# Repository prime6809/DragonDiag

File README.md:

# DragonDiag
Diagnotic card for the Dragon 32/64 and Tandy CoCo 1,2,3.

Included is the Hardware design files created in Eagle, these should be 
compatible with any version of Eagale 6.x or later. Recent versions of 
KiCad should also be able to successfully import them.
Folder: hardware

The Verilog source for the onboard XC95144XL CPLD. This can be built with
Xilinx WebPack 14.7.
Folder: cpld

The 6809 source to the diagnostic ROM generally programed into the first 
8K of the onboard flash rom. To assemble this you will need lwasm available
from http://www.lwtools.ca/ You will also need a nnix compatible make utility
I generally use cygwin, but it should be builable under Linux / Macos or 
any unix like environment with the correct tools.
Folder: src

The stl files for a case for both the diag board and the LCD display are
also provided along the the FreeCAD source files.
Folder: case

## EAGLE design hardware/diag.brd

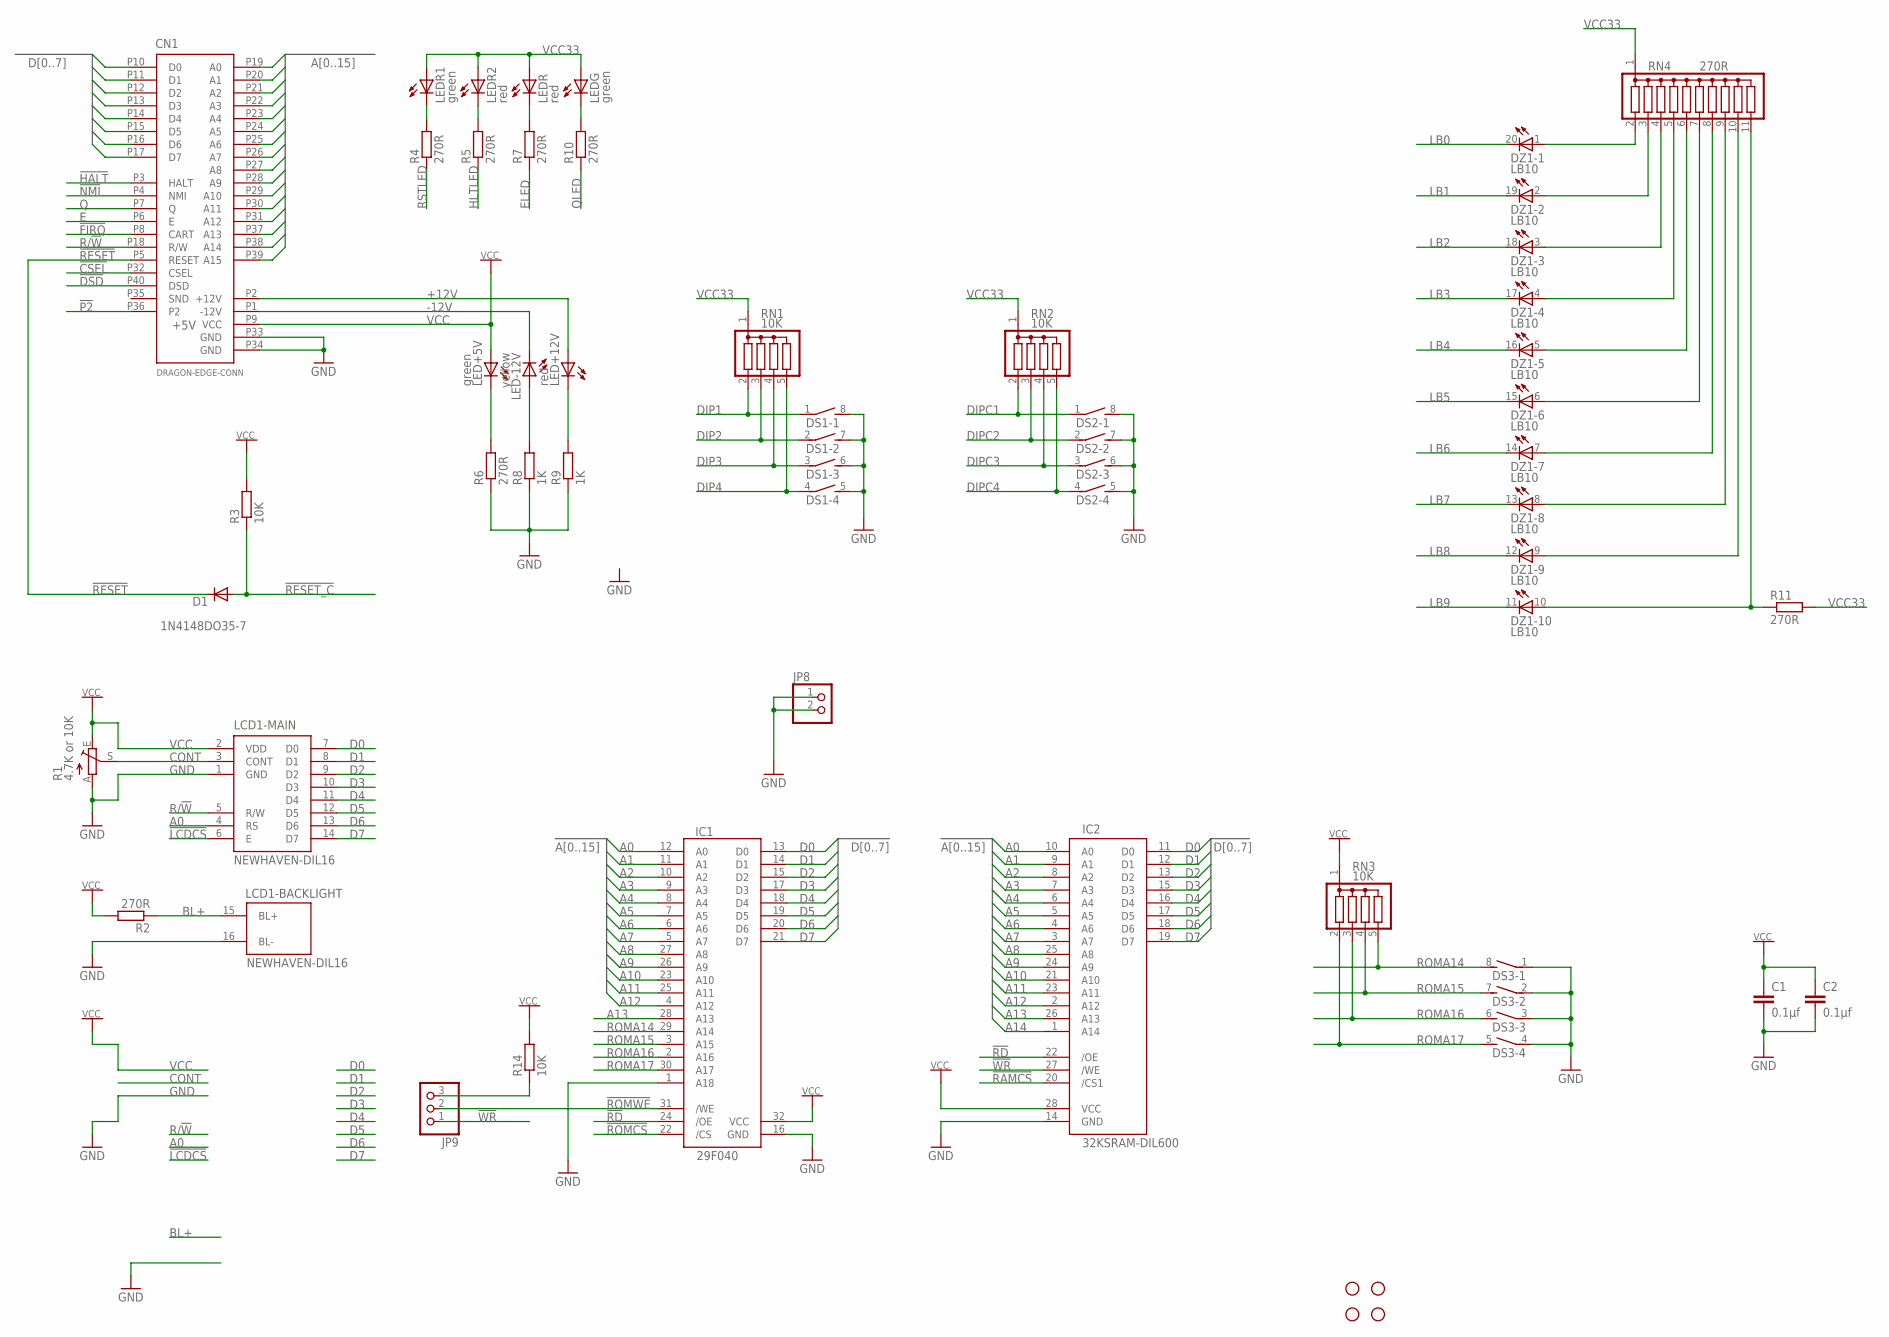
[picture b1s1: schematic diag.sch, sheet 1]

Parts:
C1, C2: 0.1µf; C025-025X050
CN1: DRAGON-EDGE-CONN; EDGE-40-01
D1: 1N4148DO35-7; DO35-7
DS1, DS2, DS3: DIP04S
DZ1: LB10
IC1: 29F040; DIL32
IC2: 32KSRAM-DIL600; DIL28-6
JP1, JP2, JP3, JP4: STAND-OFF
JP8: PINHD-1X2; 1X02
JP9: PINHD-1X3; 1X03
LCD1: NEWHAVEN-DIL16; 2X08
LED+5V: green; LED3MM
LED+12V: red; LED3MM
LED-12V: yellow; LED3MM
LEDG: green; LED3MM
LEDR, LEDR2: red; LED3MM
LEDR1: green; LED3MM
R1: 4.7K or 10K; CA9V
R2, R4, R5, R6, R7, R10, R11: 270R; 0207/10
R3: 10K; 0204/7
R8, R9: 1K; 0207/10
R14: 10K; 0207/10
RN1, RN2, RN3: 10K; SIL5
RN4: 270R; SIL11

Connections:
!CSEL: CN1.P32 (CSEL); also elsewhere on the board
!DSD: CN1.P40 (DSD); also elsewhere on the board
!FIRQ: CN1.P8 (CART); also elsewhere on the board
!HALT: CN1.P3 (HALT); also elsewhere on the board
!LCDCS: LCD1.6 (E); also elsewhere on the board
!NMI: CN1.P4 (NMI); also elsewhere on the board
!P2: CN1.P36 (P2); also elsewhere on the board
!RAMCS: IC2.20 (/CS1); also elsewhere on the board
!RD: IC1.24 (/OE), IC2.22 (/OE); also elsewhere on the board
!RESET: CN1.P5 (RESET), D1.C
!RESET_C: D1.A, R3.1; also elsewhere on the board
!ROMCS: IC1.22 (/CS); also elsewhere on the board
!ROMWE: IC1.31 (/WE), JP9.2
!WR: IC2.27 (/WE), JP9.1; also elsewhere on the board
+12V: CN1.P2 (+12V), LED+12V.A
-12V: CN1.P1 (-12V), LED-12V.K (C)
A0: CN1.P19 (A0), IC1.12 (A0), IC2.10 (A0), LCD1.4 (RS); also elsewhere on the board
A1: CN1.P20 (A1), IC1.11 (A1), IC2.9 (A1); also elsewhere on the board
A2: CN1.P21 (A2), IC1.10 (A2), IC2.8 (A2); also elsewhere on the board
A3: CN1.P22 (A3), IC1.9 (A3), IC2.7 (A3); also elsewhere on the board
A4: CN1.P23 (A4), IC1.8 (A4), IC2.6 (A4); also elsewhere on the board
A5: CN1.P24 (A5), IC1.7 (A5), IC2.5 (A5); also elsewhere on the board
A6: CN1.P25 (A6), IC1.6 (A6), IC2.4 (A6); also elsewhere on the board
A7: CN1.P26 (A7), IC1.5 (A7), IC2.3 (A7); also elsewhere on the board
A8: CN1.P27 (A8), IC1.27 (A8), IC2.25 (A8); also elsewhere on the board
A9: CN1.P28 (A9), IC1.26 (A9), IC2.24 (A9); also elsewhere on the board
A10: CN1.P29 (A10), IC1.23 (A10), IC2.21 (A10); also elsewhere on the board
A11: CN1.P30 (A11), IC1.25 (A11), IC2.23 (A11); also elsewhere on the board
A12: CN1.P31 (A12), IC1.4 (A12), IC2.2 (A12); also elsewhere on the board
A13: CN1.P37 (A13), IC1.28 (A13), IC2.26 (A13); also elsewhere on the board
A14: CN1.P38 (A14), IC2.1 (A14); also elsewhere on the board
A15: CN1.P39 (A15); also elsewhere on the board
BL+: LCD1.15 (BL+), R2.1
CONT: LCD1.3 (CONT), R1.S
D0: CN1.P10 (D0), IC1.13 (D0), IC2.11 (D0), LCD1.7 (D0); also elsewhere on the board
D1: CN1.P11 (D1), IC1.14 (D1), IC2.12 (D1), LCD1.8 (D1); also elsewhere on the board
D2: CN1.P12 (D2), IC1.15 (D2), IC2.13 (D2), LCD1.9 (D2); also elsewhere on the board
D3: CN1.P13 (D3), IC1.17 (D3), IC2.15 (D3), LCD1.10 (D3); also elsewhere on the board
D4: CN1.P14 (D4), IC1.18 (D4), IC2.16 (D4), LCD1.11 (D4); also elsewhere on the board
D5: CN1.P15 (D5), IC1.19 (D5), IC2.17 (D5), LCD1.12 (D5); also elsewhere on the board
D6: CN1.P16 (D6), IC1.20 (D6), IC2.18 (D6), LCD1.13 (D6); also elsewhere on the board
D7: CN1.P17 (D7), IC1.21 (D7), IC2.19 (D7), LCD1.14 (D7); also elsewhere on the board
DIP1: DS1.1, RN1.2; also elsewhere on the board
DIP2: DS1.2 (1), RN1.3; also elsewhere on the board
DIP3: DS1.3 (1), RN1.4; also elsewhere on the board
DIP4: DS1.4 (1), RN1.5; also elsewhere on the board
DIPC1: DS2.1, RN2.2; also elsewhere on the board
DIPC2: DS2.2 (1), RN2.3; also elsewhere on the board
DIPC3: DS2.3 (1), RN2.4; also elsewhere on the board
DIPC4: DS2.4 (1), RN2.5; also elsewhere on the board
E: CN1.P6 (E); also elsewhere on the board
ELED: R7.1; also elsewhere on the board
GND: C1.2, C2.2, CN1.P33 (GND), CN1.P34 (GND), DS1.5 (2), DS1.6 (2), DS1.7 (2), DS1.8 (2), DS2.5 (2), DS2.6 (2), DS2.7 (2), DS2.8 (2), DS3.1, DS3.2 (1), DS3.3 (1), DS3.4 (1), IC1.1 (A18), IC1.16 (GND), IC2.14 (GND), JP8.1, JP8.2, LCD1.1 (GND), LCD1.16 (BL-), R1.A, R6.1, R8.1, R9.1; also elsewhere on the board
HLTLED: R5.1; also elsewhere on the board
LB0: DZ1.20 (C); also elsewhere on the board
LB1: DZ1.19 (C); also elsewhere on the board
LB2: DZ1.18 (C); also elsewhere on the board
LB3: DZ1.17 (C); also elsewhere on the board
LB4: DZ1.16 (C); also elsewhere on the board
LB5: DZ1.15 (C); also elsewhere on the board
LB6: DZ1.14 (C); also elsewhere on the board
LB7: DZ1.13 (C); also elsewhere on the board
LB8: DZ1.12 (C); also elsewhere on the board
LB9: DZ1.11 (C); also elsewhere on the board
unnamed: LED+12V.K (C), R9.2
unnamed: LED+5V.K (C), R6.2
unnamed: DZ1.1 (A), RN4.2
unnamed: DZ1.2 (A), RN4.3
unnamed: LED-12V.A, R8.2
unnamed: DZ1.3 (A), RN4.4
unnamed: DZ1.4 (A), RN4.5
unnamed: DZ1.5 (A), RN4.6
unnamed: DZ1.6 (A), RN4.7
unnamed: LEDR.K (C), R7.2
unnamed: DZ1.7 (A), RN4.8
unnamed: DZ1.8 (A), RN4.9
unnamed: LEDG.K (C), R10.2
unnamed: DZ1.9 (A), RN4.10
unnamed: DZ1.10 (A), R11.1, RN4.11
unnamed: LEDR1.K (C), R4.2
unnamed: LEDR2.K (C), R5.2
unnamed: JP9.3, R14.1
Q: CN1.P7 (Q); also elsewhere on the board
QLED: R10.1; also elsewhere on the board
R/!W: CN1.P18 (R/W), LCD1.5 (R/W); also elsewhere on the board
ROMA14: DS3.8 (2), IC1.29 (A14), RN3.5
ROMA15: DS3.7 (2), IC1.3 (A15), RN3.4
ROMA16: DS3.6 (2), IC1.2 (A16), RN3.3
ROMA17: DS3.5 (2), IC1.30 (A17), RN3.2
RSTLED: R4.1; also elsewhere on the board
VCC: C1.1, C2.1, CN1.P9 (VCC), IC1.32 (VCC), IC2.28 (VCC), LCD1.2 (VDD), LED+5V.A, R1.E, R2.2, R3.2, R14.2, RN3.1; also elsewhere on the board
VCC33: LEDG.A, LEDR.A, LEDR1.A, LEDR2.A, R11.2, RN1.1, RN2.1, RN4.1; also elsewhere on the board

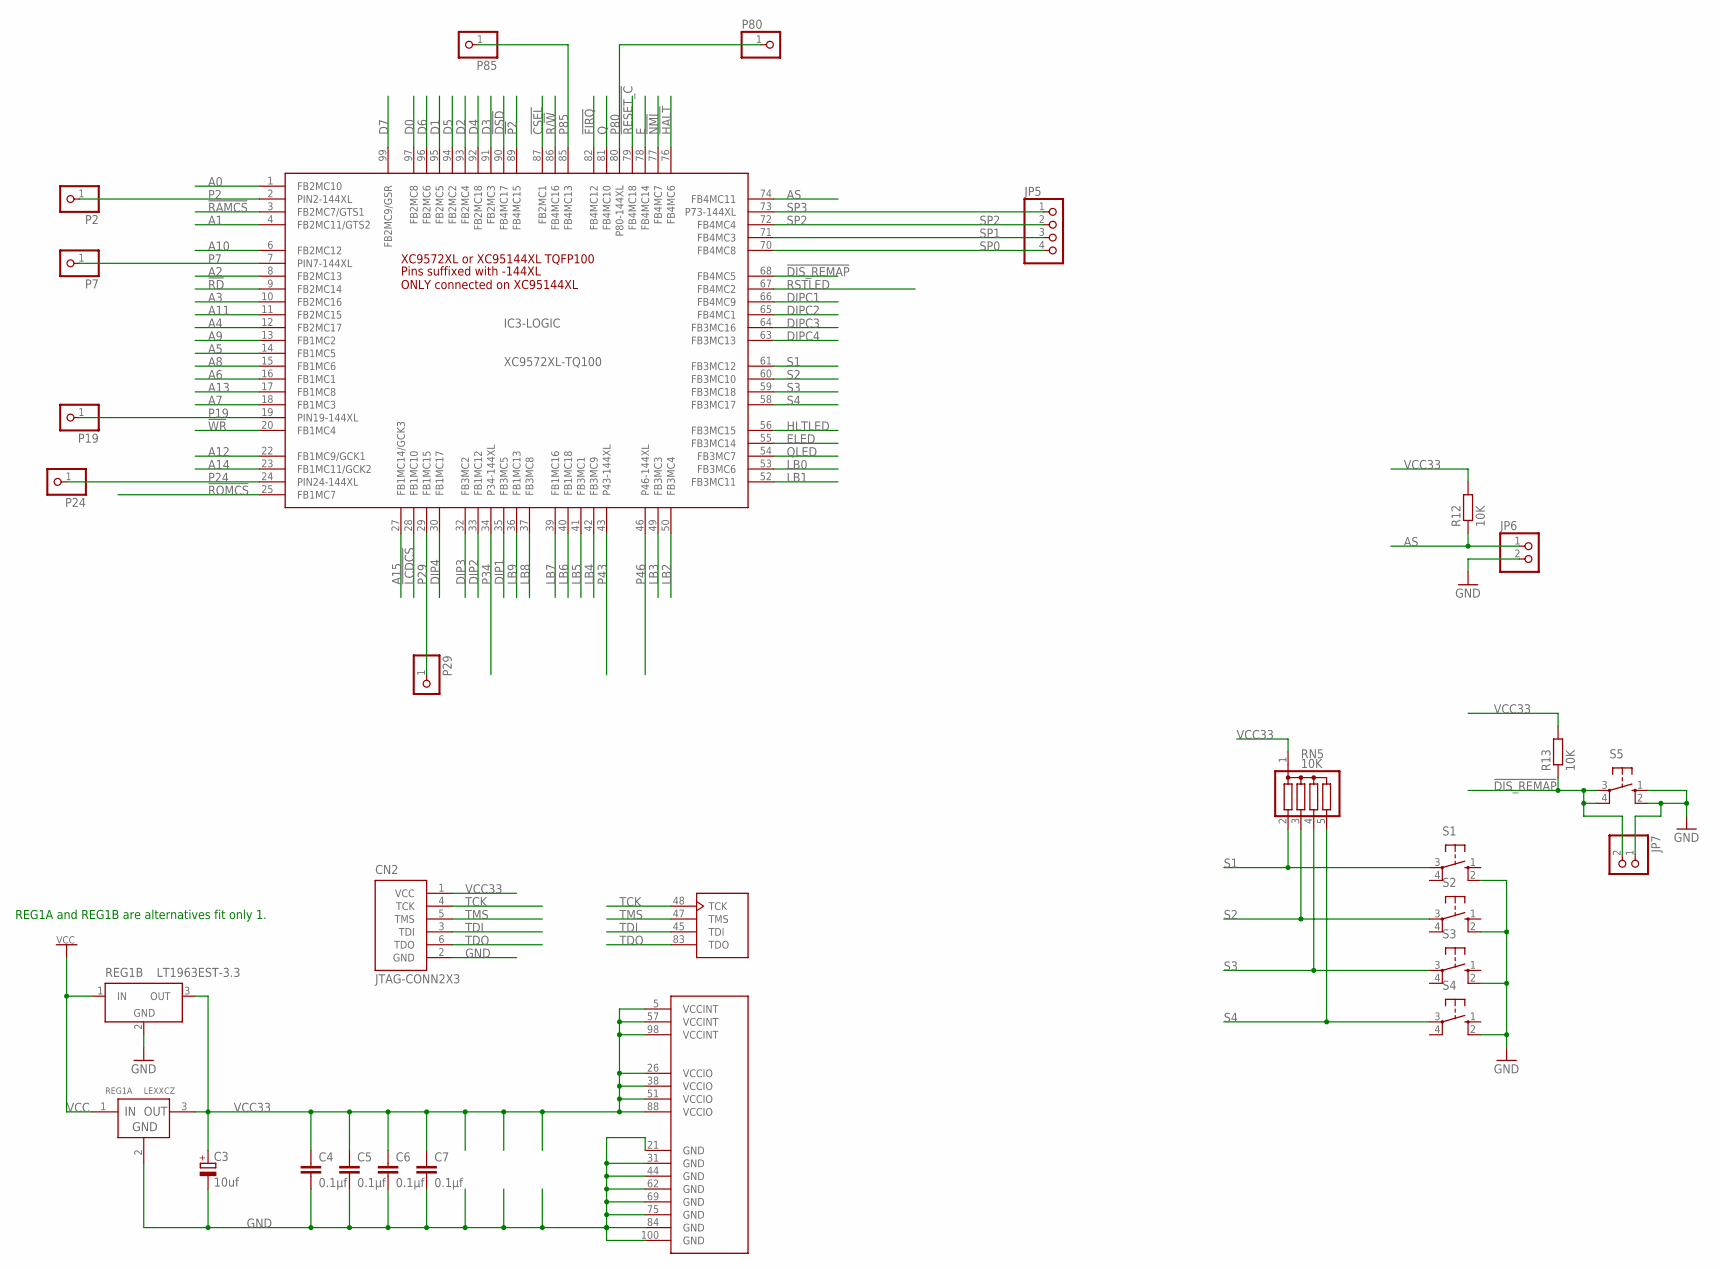
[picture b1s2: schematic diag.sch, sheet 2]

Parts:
C3: 10uf; TT2D7
C4, C5, C6, C7: 0.1µf; C025-025X050
CN2: JTAG-CONN2X3; 2X3
IC3: XC9572XL-TQ100; TQ100
JP5: PINHD-1X4; 1X04
JP6, JP7: PINHD-1X2; 1X02
P2, P7, P19, P24, P29, P80, P85: PINHD-1X1; 1X01
R12, R13: 10K; 0207/10
REG1A: LEXXCZ; TO92-
REG1B: LT1963EST-3.3; SOT223
RN5: 10K; SIL5
S1, S2, S3, S4, S5: 10-XX; B3F-10XX

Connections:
!CSEL: IC3.87 (FB2MC1); also elsewhere on the board
!DIS_REMAP: IC3.68 (FB4MC5), JP7.2, R13.1, S5.3, S5.4 (P1)
!DSD: IC3.90 (FB4MC17); also elsewhere on the board
!FIRQ: IC3.82 (FB4MC12); also elsewhere on the board
!HALT: IC3.76 (FB4MC6); also elsewhere on the board
!LCDCS: IC3.28 (FB1MC10); also elsewhere on the board
!NMI: IC3.77 (FB4MC7); also elsewhere on the board
!P2: IC3.89 (FB4MC15); also elsewhere on the board
!RAMCS: IC3.3 (FB2MC7/GTS1); also elsewhere on the board
!RD: IC3.9 (FB2MC14); also elsewhere on the board
!RESET_C: IC3.79 (FB4MC18); also elsewhere on the board
!ROMCS: IC3.25 (FB1MC7); also elsewhere on the board
!WR: IC3.20 (FB1MC4); also elsewhere on the board
A0: IC3.1 (FB2MC10); also elsewhere on the board
A1: IC3.4 (FB2MC11/GTS2); also elsewhere on the board
A2: IC3.8 (FB2MC13); also elsewhere on the board
A3: IC3.10 (FB2MC16); also elsewhere on the board
A4: IC3.12 (FB2MC17); also elsewhere on the board
A5: IC3.14 (FB1MC5); also elsewhere on the board
A6: IC3.16 (FB1MC1); also elsewhere on the board
A7: IC3.18 (FB1MC3); also elsewhere on the board
A8: IC3.15 (FB1MC6); also elsewhere on the board
A9: IC3.13 (FB1MC2); also elsewhere on the board
A10: IC3.6 (FB2MC12); also elsewhere on the board
A11: IC3.11 (FB2MC15); also elsewhere on the board
A12: IC3.22 (FB1MC9/GCK1); also elsewhere on the board
A13: IC3.17 (FB1MC8); also elsewhere on the board
A14: IC3.23 (FB1MC11/GCK2); also elsewhere on the board
A15: IC3.27 (FB1MC14/GCK3); also elsewhere on the board
AS: IC3.74 (FB4MC11), JP6.1, R12.1
D0: IC3.97 (FB2MC8); also elsewhere on the board
D1: IC3.95 (FB2MC5); also elsewhere on the board
D2: IC3.93 (FB2MC4); also elsewhere on the board
D3: IC3.91 (FB2MC3); also elsewhere on the board
D4: IC3.92 (FB2MC18); also elsewhere on the board
D5: IC3.94 (FB2MC2); also elsewhere on the board
D6: IC3.96 (FB2MC6); also elsewhere on the board
D7: IC3.99 (FB2MC9/GSR); also elsewhere on the board
DIP1: IC3.35 (FB3MC5); also elsewhere on the board
DIP2: IC3.33 (FB1MC12); also elsewhere on the board
DIP3: IC3.32 (FB3MC2); also elsewhere on the board
DIP4: IC3.30 (FB1MC17); also elsewhere on the board
DIPC1: IC3.66 (FB4MC9); also elsewhere on the board
DIPC2: IC3.65 (FB4MC1); also elsewhere on the board
DIPC3: IC3.64 (FB3MC16); also elsewhere on the board
DIPC4: IC3.63 (FB3MC13); also elsewhere on the board
E: IC3.78 (FB4MC14); also elsewhere on the board
ELED: IC3.55 (FB3MC14); also elsewhere on the board
GND: C3.-, C4.2, C5.2, C6.2, C7.2, CN2.2 (GND), IC3.21 (GND), IC3.31 (GND), IC3.44 (GND), IC3.62 (GND), IC3.69 (GND), IC3.75 (GND), IC3.84 (GND), IC3.100 (GND), JP6.2, JP7.1, REG1A.2 (GND), REG1B.2 (GND), REG1B.4 (GND), S1.2 (S1), S2.2 (S1), S3.2 (S1), S4.2 (S1), S5.1 (S), S5.2 (S1); also elsewhere on the board
HLTLED: IC3.56 (FB3MC15); also elsewhere on the board
LB0: IC3.53 (FB3MC6); also elsewhere on the board
LB1: IC3.52 (FB3MC11); also elsewhere on the board
LB2: IC3.50 (FB3MC4); also elsewhere on the board
LB3: IC3.49 (FB3MC3); also elsewhere on the board
LB4: IC3.42 (FB3MC9); also elsewhere on the board
LB5: IC3.41 (FB3MC1); also elsewhere on the board
LB6: IC3.40 (FB1MC18); also elsewhere on the board
LB7: IC3.39 (FB1MC16); also elsewhere on the board
LB8: IC3.37 (FB3MC8); also elsewhere on the board
LB9: IC3.36 (FB1MC13); also elsewhere on the board
P2: IC3.2 (PIN2-144XL), P2.1
P7: IC3.7 (PIN7-144XL), P7.1
P19: IC3.19 (PIN19-144XL), P19.1
P24: IC3.24 (PIN24-144XL), P24.1
P29: IC3.29 (FB1MC15), P29.1
P34: IC3.34 (P34-144XL)
P43: IC3.43 (P43-144XL)
P46: IC3.46 (P46-144XL)
P80: IC3.80 (P80-144XL), P80.1
P85: IC3.85 (FB4MC13), P85.1
Q: IC3.81 (FB4MC10); also elsewhere on the board
QLED: IC3.54 (FB3MC7); also elsewhere on the board
R/!W: IC3.86 (FB4MC16); also elsewhere on the board
RSTLED: IC3.67 (FB4MC2); also elsewhere on the board
S1: IC3.61 (FB3MC12), RN5.2, S1.3
S2: IC3.60 (FB3MC10), RN5.3, S2.3
S3: IC3.59 (FB3MC18), RN5.4, S3.3
S4: IC3.58 (FB3MC17), RN5.5, S4.3
SP0: IC3.70 (FB4MC8), JP5.4
SP1: IC3.71 (FB4MC3), JP5.3
SP2: IC3.72 (FB4MC4), JP5.2
SP3: IC3.73 (P73-144XL), JP5.1
TCK: CN2.4 (TCK), IC3.48 (TCK)
TDI: CN2.3 (TDI), IC3.45 (TDI)
TDO: CN2.6 (TDO), IC3.83 (TDO)
TMS: CN2.5 (TMS), IC3.47 (TMS)
VCC: REG1A.1 (IN), REG1B.1 (IN); also elsewhere on the board
VCC33: C3.+, C4.1, C5.1, C6.1, C7.1, CN2.1 (VCC), IC3.5 (VCCINT), IC3.26 (VCCIO), IC3.38 (VCCIO), IC3.51 (VCCIO), IC3.57 (VCCINT), IC3.88 (VCCIO), IC3.98 (VCCINT), R12.2, R13.2, REG1A.3 (OUT), REG1B.3 (OUT), RN5.1; also elsewhere on the board

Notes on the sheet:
REG1A and REG1B are alternatives fit only 1.

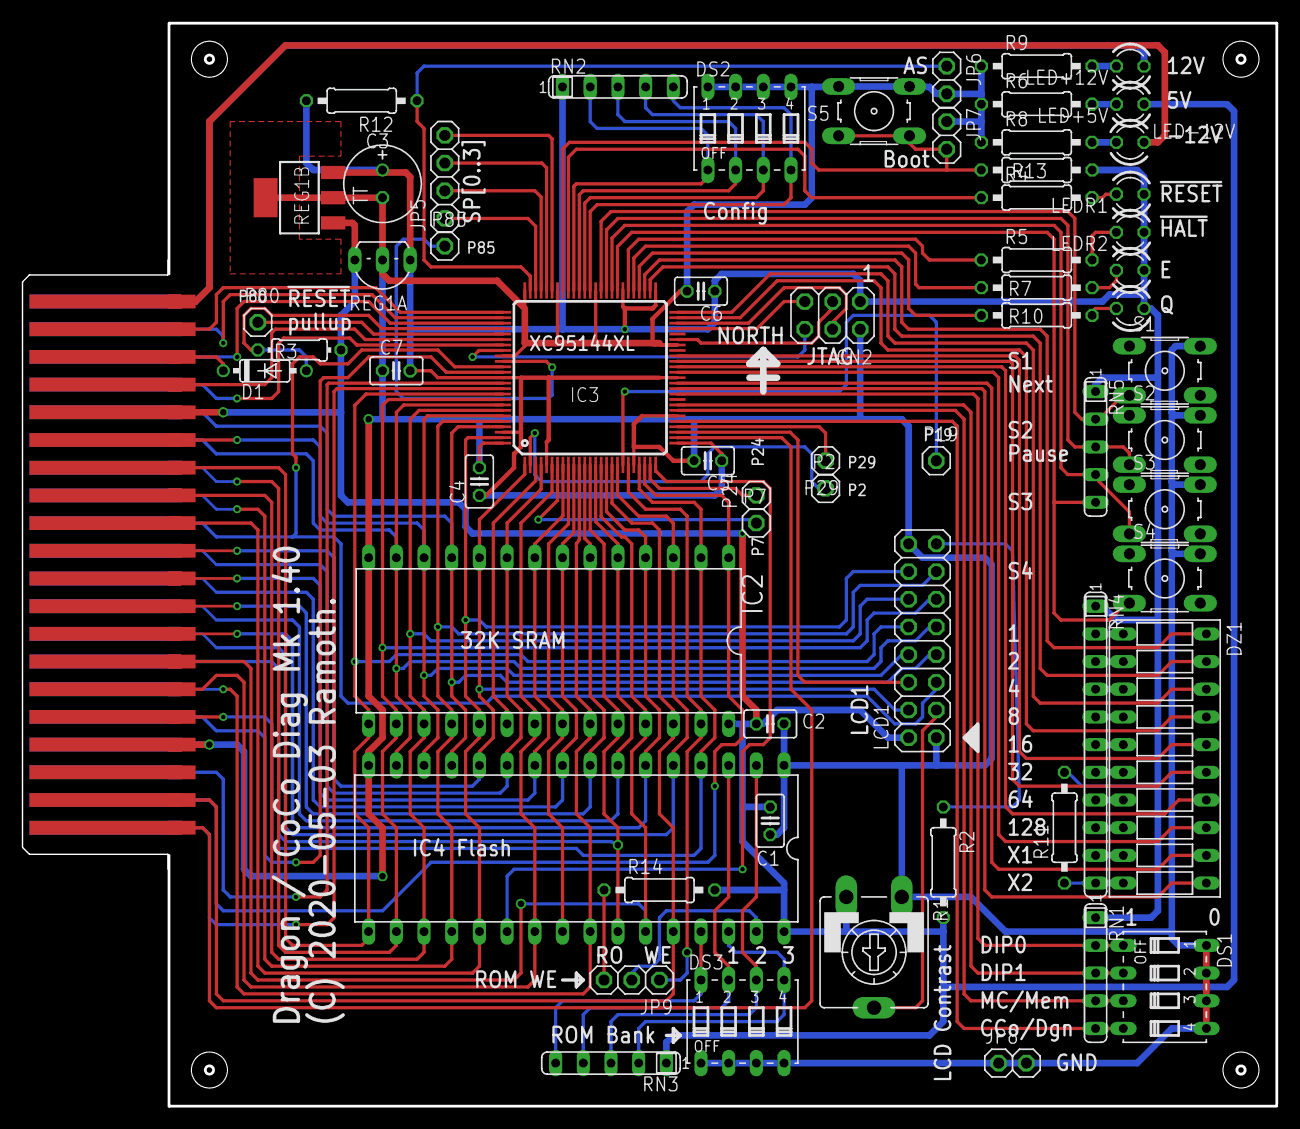
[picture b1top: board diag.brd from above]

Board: 2 copper layers, 115.0 x 99.3 mm, 67 parts (0 on the bottom side), 113 nets.

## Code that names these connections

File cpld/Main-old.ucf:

#PACE: Start of Constraints generated by PACE

#PACE: Start of PACE I/O Pin Assignments
NET "AAddr<0>"  LOC = "p54"  ; 
NET "AAddr<1>"  LOC = "p57"  ; 
NET "AAddr<2>"  LOC = "p56"  ; 
NET "AAddr<3>"  LOC = "p58"  ; 
NET "AData<0>"  LOC = "p67"  ; 
NET "AData<1>"  LOC = "p68"  ; 
NET "AData<2>"  LOC = "p69"  ; 
NET "AData<3>"  LOC = "p70"  ; 
NET "AData<4>"  LOC = "p71"  ; 
NET "AData<5>"  LOC = "p72"  ; 
NET "AData<6>"  LOC = "p74"  ; 
NET "AData<7>"  LOC = "p75"  ; 
NET "Addr<0>"  LOC = "p23"  ; 
NET "Addr<10>"  LOC = "p32"  ; 
NET "Addr<11>"  LOC = "p46"  ; 
NET "Addr<12>"  LOC = "p43"  ; 
NET "Addr<13>"  LOC = "p51"  ; 
NET "Addr<14>"  LOC = "p52"  ; 
NET "Addr<15>"  LOC = "p53"  ; 
NET "Addr<1>"  LOC = "p31"  ; 
NET "Addr<2>"  LOC = "p33"  ; 
NET "Addr<3>"  LOC = "p35"  ; 
NET "Addr<4>"  LOC = "p36"  ; 
NET "Addr<5>"  LOC = "p37"  ; 
NET "Addr<6>"  LOC = "p39"  ; 
NET "Addr<7>"  LOC = "p40"  ; 
NET "Addr<8>"  LOC = "p48"  ; 
NET "Addr<9>"  LOC = "p47"  ; 
NET "AInt"  LOC = "p66"  ; 
NET "AVRBusy"  LOC = "p62"  ;
NET "CART"  LOC = "p11"  ; 
NET "CSEL"  LOC = "p44"  ; 
NET "Data<0>"  LOC = "p12"  ; 
NET "Data<1>"  LOC = "p13"  ; 
NET "Data<2>"  LOC = "p14"  ; 
NET "Data<3>"  LOC = "p15"  ; 
NET "Data<4>"  LOC = "p17"  ; 
NET "Data<5>"  LOC = "p18"  ; 
NET "Data<6>"  LOC = "p19"  ; 
NET "Data<7>"  LOC = "p20"  ; 
NET "DSD"  LOC = "p55"  ; 
NET "E"  LOC = "p9"  ; 
NET "FData<0>"  LOC = "p77"  ; 
NET "FData<1>"  LOC = "p84"  ; 
NET "FData<2>"  LOC = "p81"  ; 
NET "FData<3>"  LOC = "p4"  ; 
NET "FData<4>"  LOC = "p79"  ; 
NET "FData<5>"  LOC = "p2"  ; 
NET "FData<6>"  LOC = "p3"  ; 
NET "FData<7>"  LOC = "p1"  ; 
NET "FRD"  LOC = "p76"  ; 
NET "FWR"  LOC = "p83"  ; 
NET "HALT"  LOC = "p5"  ; 
NET "nARD"  LOC = "p61"  ; 
NET "nAWR"  LOC = "p63"  ; 
NET "NMI"  LOC = "p6"  ; 
NET "nRAMCS"  LOC = "p26"  ; 
NET "nRD"  LOC = "p34"  ; 
NET "nROMCS"  LOC = "p45"  ; 
NET "nWR"  LOC = "p41"  ; 
NET "P2"  LOC = "p50"  ; 
NET "Q"  LOC = "p10"  ; 
NET "Reset"  LOC = "p7"  ; 
NET "RW"  LOC = "p21"  ; 
NET "RXF"  LOC = "p80"  ; 
NET "TXE"  LOC = "p82"  ; 

#PACE: Start of PACE Area Constraints

#PACE: Start of PACE Prohibit Constraints

#PACE: End of Constraints generated by PACE

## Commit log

2021-01-21 Initial checkin of diagnostic board files.
2021-01-21 Added 3D files for case. Added partscost. Updated readme.

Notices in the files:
hardware/diag.brd:
(C) 2020-05-03 Ramoth.
